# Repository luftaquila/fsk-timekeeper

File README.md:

# Formula Student Korea Timekeeper

Wireless timing system for Formula Student Korea dynamic events.

## Features

* Wireless timing with one USB master and up to five sensors
   * Wireless range over 200 m and time synchronization error below 3 µs
* Optional line-scan [photo finish camera](photofinish) with car number recognition
* [Web console](https://luftaquila.github.io/fsk-timekeeper/) with a standalone HTML file for offline use

<details>
<summary>Wireless time sync test result</summary>

https://github.com/user-attachments/assets/1cac1805-847e-4b83-8514-46a629c6ced4

* CH1 (Yellow): Master
* CH2 (Cyan) : Sensor

| Statistic | Offset |
| --- | ---: |
| Mean | +0.06 µs |
| Sample standard deviation | 0.54 µs |
| Minimum | −0.89 µs |
| Maximum | +1.14 µs |

</details>

## Usage

### 1. Prepare

1. Open the [web console](https://luftaquila.github.io/fsk-timekeeper/) in a browser with Web Serial support.
   * For offline use, download `fsk-timekeeper-console.html` from the [latest release](https://github.com/luftaquila/fsk-timekeeper/releases/latest).
2. Connect the master over USB and click `Connect` in `Settings`.
3. Power the sensors.
4. Under `Settings` → `Sensors`, assign each sensor to `Start`, `Finish`, or `Unused`.
    * Lap timing uses only the `Start` sensor.

### 2. Measure

1. Select `Start → Finish` or `Laps` in `Timing`.
2. Click `Start` to arm the timer. Timing starts on the first pass by the start sensor.
3. Complete the run:
   * `Start → Finish`: pass the finish sensor to end the run.
   * `Laps`: each subsequent pass by the start sensor records a lap.

| Start → Finish | Laps |
| :---: | :---: |
|  |  |

### 3. View and save results

Results are saved in the browser and listed in `History`.

* `Export Excel`: export results for the selected mode.
* `Backup` → `Download`: back up results from all modes and device logs as JSON.
* `Backup` → `Restore`: import a JSON backup.

> [!IMPORTANT]
> If a storage error appears, download a backup before closing the page.\
> Adding the site to your bookmarks may resolve the error.
>
> 

## Do It Yourself!

### 1. Build the PCB

1. Download `fsk-timekeeper-pcb.zip` from the [latest release](https://github.com/luftaquila/fsk-timekeeper/releases/latest) and extract it.
2. Place a JLCPCB PCBA order for five boards (the minimum quantity) using the included GERBER, BOM, and CPL files.

### 2. Solder the parts

<details>
<summary>Bill of materials</summary>

| Qty | Part | Image |
| ---: | --- | :---: |
| 5x | Assembled `fsk-timekeeper` PCB | |
| 5x | 22 µH SMD power inductor, 0630 package |  |
| 5x | `SuperMini nRF52840` development board |  |
| 5x | `Ra-01SH` LoRa module |  |
| 5x | LoRa antenna with IPEX-to-SMA female cable |  |
| 4x | Single-cell SMD 18650 battery holder and 18650 battery |  |
| 4x | `MTS-102` mini toggle switch |  |
| 4x | [Autonics BA2M-DDT](https://www.autonics.com/kr/model/BA2M-DDT) diffuse reflective photoelectric sensor |  |
| 4x | [Molex 5569-04A2 (39300040)](https://www.molex.com/en-us/products/part-detail/39300040) board connector |  |
| 4x | [Molex 5557-04R (39012040)](https://www.molex.com/en-us/products/part-detail/39012040) cable housing |  |
| 12x | [Molex 5556T (39000038)](https://www.molex.com/en-us/products/part-detail/39000038) crimp terminal |  |
| 1x | `ATGM336H` GPS module with antenna |  |

</details>

> [!NOTE]
> The JLCPCB PCBA order above costs about <span>$</span>7, excluding shipping.\
> The full set of parts costs about <span>$</span>40 on AliExpress, excluding BA2M-DDT sensors and 18650 batteries.

> [!IMPORTANT]
> Solder `U2` first. Installing `U1` first makes `U2` harder to solder.

1. All boards: solder `U2` (Ra-01SH), `U1` (SuperMini nRF52840), and `L1` (22 µH 0630 inductor).
2. Master: solder the GPS module at `U4` and connect its antenna.
3. Sensors: solder the battery holder at `BT1` and the `5569-04A2` connector at `J1`, then wire the toggle switch to `SW1`.
4. Connect each LoRa module to an IPEX-to-SMA cable.

| 3D view | Layout |
| :---: | :---: |
|  |  |

### 3. Housing assembly

Required per sensor: 4x M2 × 8 mm and 3x M3 × 14 mm hex bolts.

1. Download `fsk-timekeeper-3d.zip` from the [latest release](https://github.com/luftaquila/fsk-timekeeper/releases/latest) and extract it.
2. 3D-print 1x `master.stl`, 4x `sensor.stl`, and 4x `sensor-holder.stl`.
   * With the [photo finish camera](photofinish), print `photofinish.stl` instead of `master.stl`.
3. Mount the SMA connectors and attach the LoRa antennas.
4. Mount the switches and insert 18650 batteries into the sensor housings.
5. Secure each PCB between the base and lid with M2 bolts.
6. Secure the `BA2M-DDT` sensor to the holder with M3 bolts, then mount the holder on a tripod.

### 4. Upload firmware and configure devices

1. In console's `Firmware Upgrade`, select `fsk-timekeeper-firmware.zip` and click `Upgrade`.
2. Select the port and keep the USB cable connected until the upload is complete.
   * If a new board does not enter bootloader mode automatically, short the `RST` pin to `GND` twice quickly.
3. Click `Reconnect` and select the board to verify the new firmware version.
4. Generate a new key under `Radio Key` and apply it to the first board.
5. Set up the remaining boards with the same firmware and radio key.

> [!IMPORTANT]
> The master and all sensors must use the same firmware version, radio settings, and key.

> [!TIP]
> The board connected over USB acts as the master. Battery-powered boards act as sensors.

### 5. Connect the sensors

| Pinout | Wiring |
| :---: | :---: |
|  |  |

## Development

<details>
<summary>Click to expand</summary>

### Firmware

* Requires: Arm GNU Toolchain (`arm-none-eabi-gcc`, newlib-nano), Make, Python 3

  ```sh
  make -C device/firmware test
  make -C device/firmware
  ```

### Web console

* Requires: Node.js 22

  ```sh
  cd console
  npm ci
  npm test
  npm run dev           # development server
  npm run build:single  # standalone HTML at dist-single/index.html
  ```

### PCB

* Requires: KiCad 10+
* Open [fsk-timekeeper.kicad_pro](device/hardware/fsk-timekeeper.kicad_pro)

### Housing 3D model

* Requires: OpenSCAD Nightly

  ```sh
  make -C device/3d
  ```

</details>

## LICENSE

For non-commercial use only:

```
"THE BEERWARE LICENSE" (Revision 42):
LUFT-AQUILA wrote this project. As long as you retain this notice,
you can do whatever you want with this stuff. If we meet someday,
and you think this stuff is worth it, you can buy me a beer in return.
```

이 저장소의 모든 내용은 비상업적 용도로 자유롭게 사용할 수 있습니다.\
이 프로젝트가 마음에 든다면, 언젠가 우리가 만나게 되었을 때 맥주 한 잔 사 주세요.

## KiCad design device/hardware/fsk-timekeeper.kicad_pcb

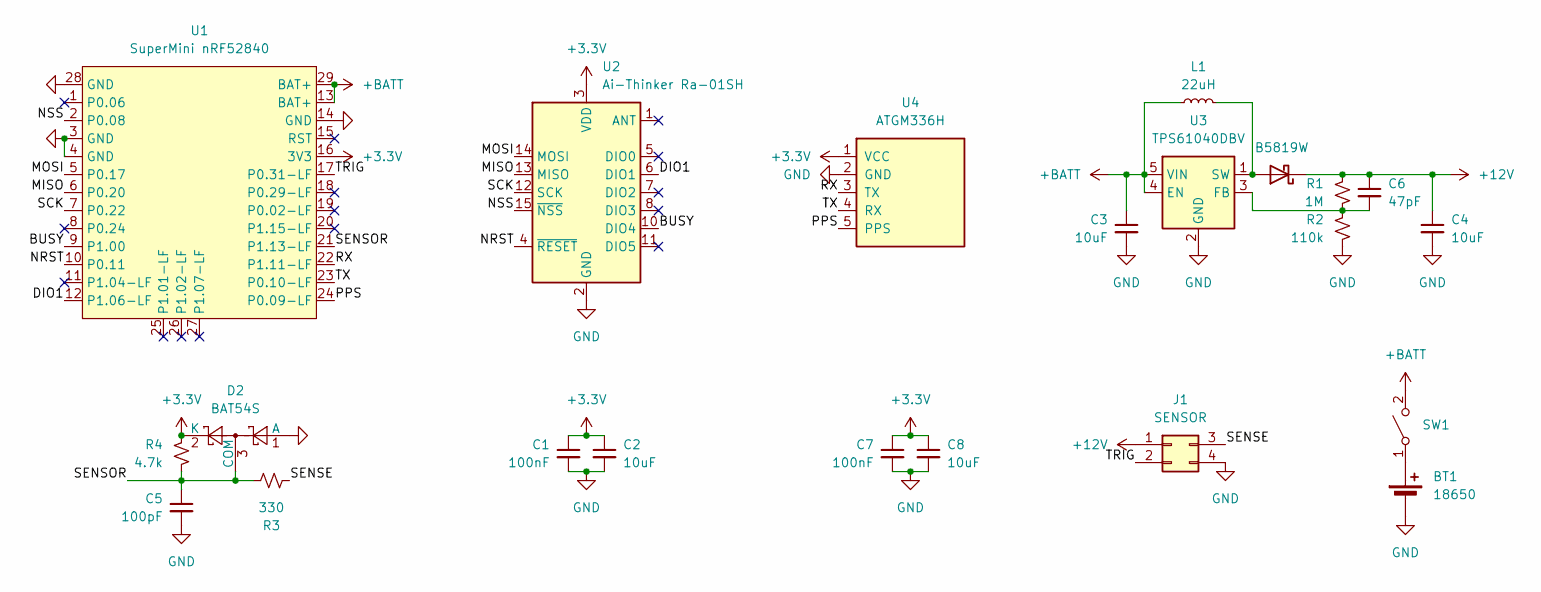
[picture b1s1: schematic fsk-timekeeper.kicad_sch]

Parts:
BT1: 18650; BatteryHolder_Keystone_1042_1x18650
C1, C7: 100nF; C_0603_1608Metric; LCSC C14663
C2, C3, C4, C8: 10uF; C_0603_1608Metric; LCSC C96446
C5: 100pF; C_0603_1608Metric; LCSC C14858
C6: 47pF; C_0603_1608Metric; LCSC C1671
D1: B5819W; D_SOD-123; LCSC C8598
D2: BAT54S; SOT-23; LCSC C7420333
J1: SENSOR; Molex_Mini-Fit_Jr_5569-04A2_2x02_P4.20mm_Horizontal
L1: 22uH; L_Sunlord_MWSA0603S
R1: 1M; R_0603_1608Metric; LCSC C22935
R2: 110k; R_0603_1608Metric; LCSC C25805
R3: 330; R_0603_1608Metric; LCSC C23138
R4: 4.7k; R_0603_1608Metric; LCSC C23162
SW1: POWER; PinHeader_1x02_P2.54mm_Vertical
U1: SuperMini nRF52840; SuperMini_NRF52840
U2: Ai-Thinker Ra-01SH; Ai-Thinker-Ra-01-LoRa
U3: TPS61040DBV; SOT-23-5; LCSC C7722
U4: ATGM336H; ATGM336H_GPS_Module

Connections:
+3.3V: C1.1, C2.1, C7.1, C8.1, D2.2 (K), R4.2, U1.16 (3V3), U2.3 (VDD), U4.1 (VCC)
+12V: C4.1, C6.1, D1.1 (K), J1.1, R1.1
+BATT: C3.1, L1.1, SW1.2 (B), U1.13 (BAT+), U1.29 (BAT+), U3.4 (EN), U3.5 (VIN)
/BUSY: U1.9 (P1.00), U2.10 (DIO4)
/DIO1: U1.12 (P1.06-LF), U2.6 (DIO1)
/MISO: U1.6 (P0.20), U2.13 (MISO)
/MOSI: U1.5 (P0.17), U2.14 (MOSI)
/NRST: U1.10 (P0.11), U2.4 (~RESET)
/NSS: U1.2 (P0.08), U2.15 (~NSS)
/PPS: U1.24 (P0.09-LF), U4.5 (PPS)
/RX: U1.22 (P1.11-LF), U4.3 (TX)
/SCK: U1.7 (P0.22), U2.12 (SCK)
/SENSE: J1.3, R3.1
/SENSOR: C5.1, D2.3 (COM), R3.2, R4.1, U1.21 (P1.13-LF)
/TRIG: J1.2, U1.17 (P0.31-LF)
/TX: U1.23 (P0.10-LF), U4.4 (RX)
GND: BT1.2 (-), C1.2, C2.2, C3.2, C4.2, C5.2, C7.2, C8.2, D2.1 (A), J1.4, R2.2, U1.3 (GND), U1.4 (GND), U1.14 (GND), U1.28 (GND), U2.2 (GND), U2.9 (GND), U2.16 (GND), U3.2 (GND), U4.2 (GND)
unnamed: BT1.1 (+), SW1.1 (A)
unnamed: D1.2 (A), L1.2, U3.1 (SW)
unnamed: C6.2, R1.2, R2.1, U3.3 (FB)

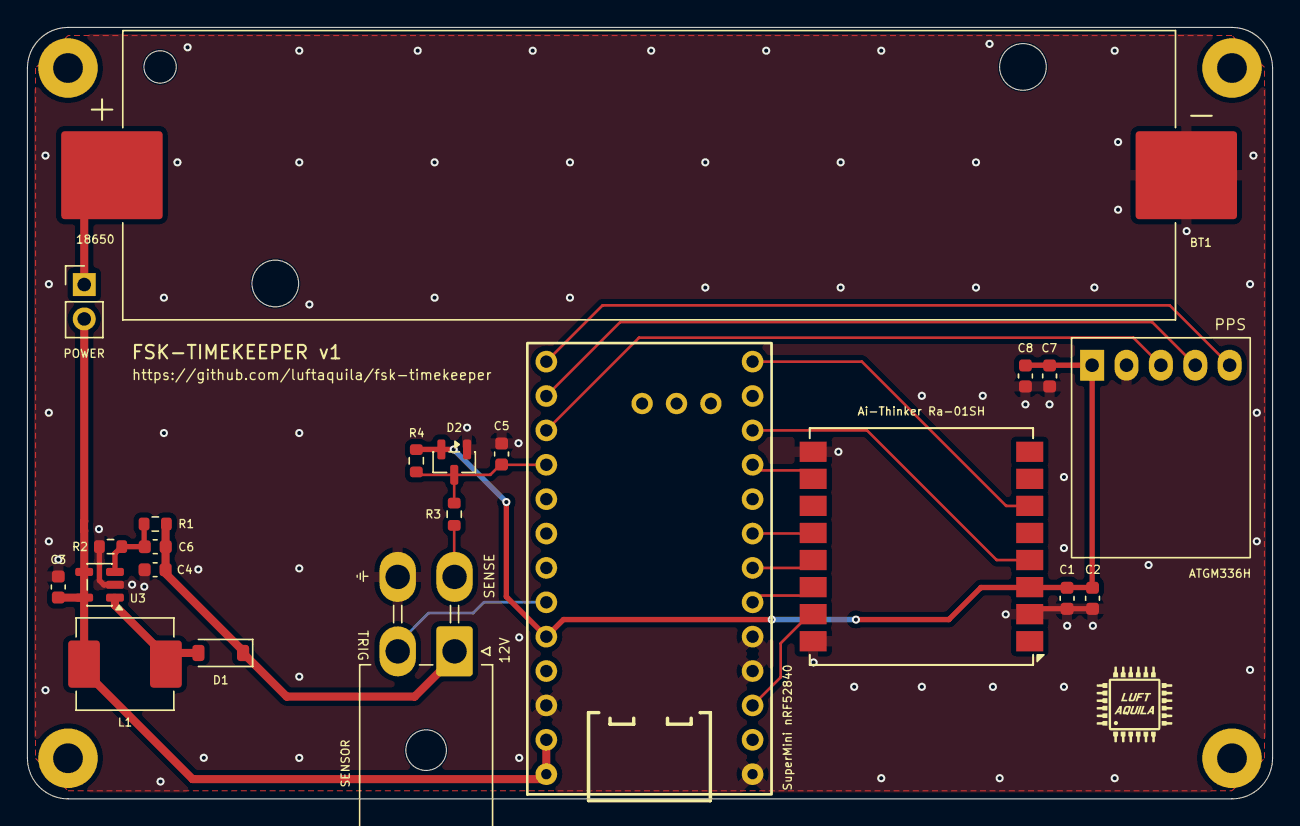
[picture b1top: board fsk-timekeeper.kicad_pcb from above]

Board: 2 copper layers, 92.0 x 57.0 mm, 22 parts (0 on the bottom side), 20 nets.

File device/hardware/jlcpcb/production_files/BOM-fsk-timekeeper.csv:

Comment,Designator,Footprint,LCSC,Quantity
100nF,"C1,C7",C_0603_1608Metric,C14663,2
100pF,C5,C_0603_1608Metric,C14858,1
10uF,"C2,C3,C4,C8",C_0603_1608Metric,C96446,4
110k,R2,R_0603_1608Metric,C25805,1
1M,R1,R_0603_1608Metric,C22935,1
330,R3,R_0603_1608Metric,C23138,1
4.7k,R4,R_0603_1608Metric,C23162,1
47pF,C6,C_0603_1608Metric,C1671,1
B5819W,D1,D_SOD-123,C8598,1
BAT54S,D2,SOT-23,C7420333,1
TPS61040DBV,U3,SOT-23-5,C7722,1

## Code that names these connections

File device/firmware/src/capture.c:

#include "capture.h"

#include "config.h"
#include "board.h"
#include "gpio.h"
#include "nrf.h"

/* TIMER1 timebase, TIMER2 micros, TIMER3 edge count; SoftDevice never on: all GPIOTE/PPI free. */
#define CAP_GPIOTE_DIO1 0
#define CAP_GPIOTE_SENS 1
#define CAP_GPIOTE_PPS  2
#define CAP_PPI_DIO1    0
#define CAP_PPI_SENS    1
#define CAP_PPI_PPS     2
#define CAP_CC_DIO1     0 /* TIMER1->CC[] latched by DIO1 */
#define CAP_CC_NOW      1 /* TIMER1->CC[] for on-demand reads */
#define CAP_CC_SENS     2 /* TIMER1->CC[] latched by SENSOR */
#define CAP_CC_PPS      3 /* TIMER1->CC[] latched by PPS */
#define SENSOR_RING_LEN 64u /* power of two */

#define DIO1_PIN (PIN_LORA_DIO1 % 32u)
#define DIO1_PRT (PIN_LORA_DIO1 / 32u)
#define SENS_PIN (PIN_SENSOR_IN % 32u)
#define SENS_PRT (PIN_SENSOR_IN / 32u)
#define PPS_PIN  (PIN_GPS_PPS % 32u)
#define PPS_PRT  (PIN_GPS_PPS / 32u)

static volatile uint32_t s_ring_tick[SENSOR_RING_LEN];
static volatile uint32_t s_ring_seq[SENSOR_RING_LEN];
static volatile uint8_t s_ring_xtal[SENSOR_RING_LEN];
static volatile uint32_t s_sensor_seq;
static volatile uint32_t s_loss_first_seq, s_loss_last_seq, s_loss_first_tick, s_loss_last_tick;
static volatile int s_loss_pending, s_loss_unknown;
static volatile uint8_t s_head;
static volatile uint8_t s_tail;
static volatile uint16_t s_overflow;

static uint32_t sensor_count(void)
{
#ifdef CAPTURE_HOST_TEST
    extern uint32_t capture_test_count(void);
    return capture_test_count();
#else
    NRF_TIMER3->TASKS_CAPTURE[0] = 1;
    return NRF_TIMER3->CC[0];
#endif
}

/* Every edge is counted even while the CPU stalls; pair tick and seq only on a stable snapshot. */
void GPIOTE_IRQHandler(void)
{
    if (!NRF_GPIOTE->EVENTS_IN[CAP_GPIOTE_SENS]) { return; }
    NRF_GPIOTE->EVENTS_IN[CAP_GPIOTE_SENS] = 0;
    uint32_t before = sensor_count();
    uint32_t tick = NRF_TIMER1->CC[CAP_CC_SENS];
    uint32_t seq = sensor_count();
    uint32_t delta = seq - s_sensor_seq;
    if (delta == 0u) { return; } /* a later edge already included by the previous ISR */
    int unknown = delta != 1u || before != seq || NRF_GPIOTE->EVENTS_IN[CAP_GPIOTE_SENS];
    uint32_t first = s_sensor_seq + 1u;
    s_sensor_seq = seq;
    uint8_t head = s_head;
    uint8_t next = (uint8_t)((head + 1u) & (SENSOR_RING_LEN - 1u));
    if (unknown || next == s_tail || s_loss_pending) {
        if (delta > (uint32_t)(UINT16_MAX - s_overflow)) { s_overflow = UINT16_MAX; }
        else { s_overflow = (uint16_t)(s_overflow + delta); }
        if (!s_loss_pending) {
            s_loss_first_seq = first;
            s_loss_first_tick = tick;
            s_loss_unknown = 0;
        }
        s_loss_last_seq = seq;
        s_loss_last_tick = tick;
        s_loss_unknown |= unknown;
        s_loss_pending = 1;
    } else {
        s_ring_tick[head] = tick;
        s_ring_seq[head] = seq;
        s_ring_xtal[head] = (uint8_t)board_hfclk_xtal();
        __DMB();
        s_head = next;
    }
}

static uint32_t gpiote_event(uint32_t pin, uint32_t port, uint32_t polarity)
{
    return ((uint32_t)GPIOTE_CONFIG_MODE_Event << GPIOTE_CONFIG_MODE_Pos) |
           (pin << GPIOTE_CONFIG_PSEL_Pos) | (port << GPIOTE_CONFIG_PORT_Pos) |
           (polarity << GPIOTE_CONFIG_POLARITY_Pos);
}

void capture_init(void)
{
    NRF_TIMER1->TASKS_STOP = 1;
    NRF_TIMER1->MODE = TIMER_MODE_MODE_Timer;
    NRF_TIMER1->BITMODE = TIMER_BITMODE_BITMODE_32Bit;
    NRF_TIMER1->PRESCALER = 0; /* 16 MHz */
    NRF_TIMER1->TASKS_CLEAR = 1;
    NRF_TIMER1->TASKS_START = 1;

    NRF_GPIOTE->CONFIG[CAP_GPIOTE_DIO1] = gpiote_event(DIO1_PIN, DIO1_PRT, GPIOTE_CONFIG_POLARITY_LoToHi);
    NRF_GPIOTE->EVENTS_IN[CAP_GPIOTE_DIO1] = 0;
    NRF_PPI->CH[CAP_PPI_DIO1].EEP = (uint32_t)&NRF_GPIOTE->EVENTS_IN[CAP_GPIOTE_DIO1];
    NRF_PPI->CH[CAP_PPI_DIO1].TEP = (uint32_t)&NRF_TIMER1->TASKS_CAPTURE[CAP_CC_DIO1];
    NRF_PPI->CHENSET = (1UL << CAP_PPI_DIO1);
}

/* SENSOR falling edge -> TIMER1 CC and TIMER3 count on one PPI channel and its fork. */
static void sensor_edge_hw(void)
{
    NRF_TIMER3->TASKS_STOP = 1;
    NRF_TIMER3->MODE = TIMER_MODE_MODE_Counter;
    NRF_TIMER3->BITMODE = TIMER_BITMODE_BITMODE_32Bit;
    NRF_TIMER3->TASKS_CLEAR = 1;
    NRF_TIMER3->TASKS_START = 1;
    gpio_cfg_input_pullup(PIN_SENSOR_IN); /* NPN open collector */
    NRF_GPIOTE->CONFIG[CAP_GPIOTE_SENS] = gpiote_event(SENS_PIN, SENS_PRT, GPIOTE_CONFIG_POLARITY_HiToLo);
    NRF_GPIOTE->EVENTS_IN[CAP_GPIOTE_SENS] = 0;
    NRF_PPI->CH[CAP_PPI_SENS].EEP = (uint32_t)&NRF_GPIOTE->EVENTS_IN[CAP_GPIOTE_SENS];
    NRF_PPI->CH[CAP_PPI_SENS].TEP = (uint32_t)&NRF_TIMER1->TASKS_CAPTURE[CAP_CC_SENS];
    NRF_PPI->FORK[CAP_PPI_SENS].TEP = (uint32_t)&NRF_TIMER3->TASKS_COUNT;
    NRF_PPI->CHENSET = (1UL << CAP_PPI_SENS);
}

void capture_sensor_enable(void)
{
    sensor_edge_hw();
    NRF_GPIOTE->INTENSET = (1UL << (GPIOTE_INTENSET_IN0_Pos + CAP_GPIOTE_SENS));
    NVIC_ClearPendingIRQ(GPIOTE_IRQn);
    NVIC_SetPriority(GPIOTE_IRQn, 3);
    NVIC_EnableIRQ(GPIOTE_IRQn);
}

void capture_pps_enable(void)
{
    /* Rising edge = UTC second (ATGM336H), polled like DIO1; pull-down: no GPS, no edges. */
    gpio_cfg_input_pulldown(PIN_GPS_PPS);
    NRF_GPIOTE->CONFIG[CAP_GPIOTE_PPS] = gpiote_event(PPS_PIN, PPS_PRT, GPIOTE_CONFIG_POLARITY_LoToHi);
    NRF_GPIOTE->EVENTS_IN[CAP_GPIOTE_PPS] = 0;
    NRF_PPI->CH[CAP_PPI_PPS].EEP = (uint32_t)&NRF_GPIOTE->EVENTS_IN[CAP_GPIOTE_PPS];
    NRF_PPI->CH[CAP_PPI_PPS].TEP = (uint32_t)&NRF_TIMER1->TASKS_CAPTURE[CAP_CC_PPS];
    NRF_PPI->CHENSET = (1UL << CAP_PPI_PPS);
}

/* 32 -> 64-bit extension: bump the high word whenever the low word wrapped. */
static uint64_t s_base;
static uint32_t s_prev;

uint32_t capture_now32(void)
{
    NRF_TIMER1->TASKS_CAPTURE[CAP_CC_NOW] = 1;
    return NRF_TIMER1->CC[CAP_CC_NOW];
}

uint64_t capture_now64(void)
{
    uint32_t low = capture_now32();
    if (low < s_prev) {
        s_base += (uint64_t)1 << 32;
    }
    s_prev = low;
    return s_base + low;
}

/* Widen a capture latched less than 2^32 ticks ago. */
static uint64_t widen(uint32_t cap_low)
{
    uint64_t now = capture_now64();
    uint32_t delta = (uint32_t)now - cap_low;
    return now - delta;
}

int capture_dio1_get(uint64_t *tick)
{
    if (NRF_GPIOTE->EVENTS_IN[CAP_GPIOTE_DIO1] == 0) {
        return 0;
    }
    NRF_GPIOTE->EVENTS_IN[CAP_GPIOTE_DIO1] = 0;
    *tick = widen(NRF_TIMER1->CC[CAP_CC_DIO1]);
    return 1;
}

int capture_sensor_get(uint64_t *tick, uint32_t *seq, int *clock_xtal)
{
    uint8_t tail = s_tail;
    if (tail == s_head) { return 0; }
    uint32_t low = s_ring_tick[tail];
    *seq = s_ring_seq[tail];
    *clock_xtal = s_ring_xtal[tail];
    __DMB();
    s_tail = (uint8_t)((tail + 1u) & (SENSOR_RING_LEN - 1u));
    *tick = widen(low);
    return 1;
}

int capture_sensor_loss(uint64_t *first_tick, uint64_t *last_tick, uint32_t *first_seq, uint32_t *last_seq)
{
    NVIC_DisableIRQ(GPIOTE_IRQn);
    if (!s_loss_pending) { NVIC_EnableIRQ(GPIOTE_IRQn); return 0; }
    *first_tick = widen(s_loss_first_tick); *last_tick = widen(s_loss_last_tick);
    *first_seq = s_loss_first_seq; *last_seq = s_loss_last_seq;
    int result = s_loss_unknown ? CAPTURE_LOSS_UNKNOWN : CAPTURE_LOSS_KNOWN;
    s_loss_pending = s_loss_unknown = 0;
    NVIC_EnableIRQ(GPIOTE_IRQn);
    return result;
}

int capture_sensor_checkpoint(uint64_t *tick, uint32_t *seq)
{
    NVIC_DisableIRQ(GPIOTE_IRQn);
    uint32_t before = sensor_count();
    *tick = capture_now64();
    uint32_t after = sensor_count();
    int empty = before == after && after == s_sensor_seq && s_head == s_tail &&
                !s_loss_pending && !NRF_GPIOTE->EVENTS_IN[CAP_GPIOTE_SENS];
    *seq = s_sensor_seq;
    NVIC_EnableIRQ(GPIOTE_IRQn);
    return empty;
}

uint16_t capture_sensor_overflow(void)
{
    return s_overflow;
}

/* Up to 58 k strobes/s: no ISR, the main loop samples the latest CC and the count. */
void capture_strobe_enable(void)
{
    sensor_edge_hw();
}

void capture_strobe_reset(void)
{
    NRF_TIMER3->TASKS_CLEAR = 1;
    NRF_GPIOTE->EVENTS_IN[CAP_GPIOTE_SENS] = 0;
}

uint32_t capture_strobe_count(void)
{
    return sensor_count();
}

int capture_strobe_sample(uint32_t *count, uint64_t *tick)
{
    uint32_t before = sensor_count();
    uint32_t low = NRF_TIMER1->CC[CAP_CC_SENS];
    uint32_t after = sensor_count();
    if (before != after || after == 0u) { return 0; }
    *count = after;
    *tick = widen(low);
    return 1;
}

int capture_pps_get(uint64_t *tick)
{
    if (NRF_GPIOTE->EVENTS_IN[CAP_GPIOTE_PPS] == 0) {
        return 0;
    }
    NRF_GPIOTE->EVENTS_IN[CAP_GPIOTE_PPS] = 0;
    *tick = widen(NRF_TIMER1->CC[CAP_CC_PPS]);
    return 1;
}
